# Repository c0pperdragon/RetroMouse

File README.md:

# RetroMouse
Adapter to attach PS/2 compatible mice to retro computers

## Motivation

I wanted to try to make such an adapter using one attiny1604 microcontroller 
with only the minimum additional circuitry.
This part also was one of the few that mouser actually had in stock.

## Mouse compatibility

The USB socket suggests that any USB mouse can be used, but that is actually not true. In 
reality the adapter only supports the simpler PS/2 interface protocol which can be handled by
regular microcontrollers just well.

For this to work, the mouse must be able to optionally support PS/2 if needed. Luckily this
compatibility is present in quite many devices, especially in the cheap and simple variants.
Unluckily on the other hand, this compatibilty depends on the specific controller IC the
manufacturer used for the mouse and can not really be guessed from the outside.
When PS/2 compatibility is not directly advertised, the only thing to do is just try.

## Arduino development

The microcontroller is supported by the Arduino IDE (using the megaTinyCore add-on).
To modify the firmware, you need a programmer device to re-flash the microcontroller
using the UDPI pin. Details on this process are available on the megaTinyCore webpage.

## Compatibility

This adapter works with Amiga and C64 computers and can auto-detect the host machine.
Further machines (for example Atari ST) may be supported in the future. 

## C64 input modes

From power-up, the adapter emulates the Commodore 1351 mouse. If you want to 
emulate a pair of paddles instead (to play Arkanoid, for example) hold down the right mouse button 
and click the left button 5 times. Doing the same thing with 6 left clicks switches back
to standard mode.

## Attention! No Hot-Plugging

The adapter is not designed to be hot-plugged into the host machine or the mouse to be hot-plugged
into the adapter. Make sure to always power down the host when changing configuration.

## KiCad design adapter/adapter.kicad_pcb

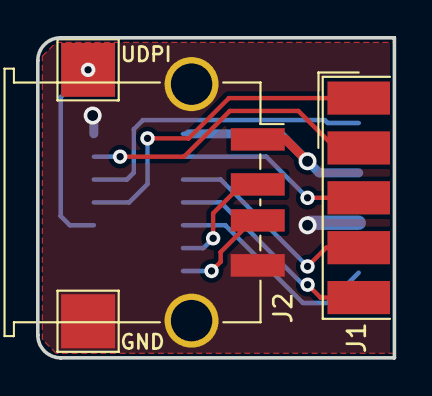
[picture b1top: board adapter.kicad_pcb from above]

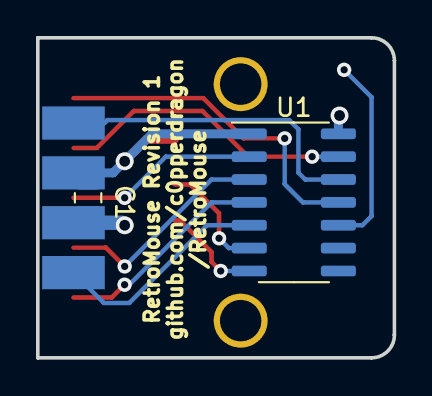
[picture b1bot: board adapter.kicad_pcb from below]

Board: 2 copper layers, 19.8 x 17.8 mm, 6 parts (2 on the bottom side), 12 nets.

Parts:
C1: 10uF; C_0805_2012Metric_Pad1.18x1.45mm_HandSolder
J1: DB9_Female; DSUB-9_Female_EdgeMount_P2.77mm
J2: USB_A; USB_A_TE_292303-7_Horizontal
J3, J4: Conn_01x01; TestPoint_Pad_3.0x3.0mm
U1: ATtiny1604-SS; SOIC-14_3.9x8.7mm_P1.27mm

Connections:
+5V: C1.1, J1.7, J2.1 (VBUS), U1.1 (VCC)
/CLOCK: J2.3 (D+), U1.7 (PB2)
/DATA: J2.2 (D-), U1.6 (PB3)
/UDPI: J4.1, U1.10 (~RESET/PA0)
GND: C1.2, J1.8, J2.4 (GND), J2.5 (Shield), J3.1, U1.14 (GND)
unnamed: J1.1, U1.11 (PA1)
unnamed: J1.2, U1.13 (PA3)
unnamed: J1.3, U1.2 (PA4)
unnamed: J1.4, U1.3 (PA5)
unnamed: J1.5, U1.4 (PA6)
unnamed: J1.6, U1.12 (PA2)
unnamed: J1.9, U1.5 (PA7)

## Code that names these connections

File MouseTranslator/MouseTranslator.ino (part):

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#include "PS2MouseHandler.h"

#define DEBUG       PIN_PB1
#define MOUSE_DATA  PIN_PB3
#define MOUSE_CLOCK PIN_PB2
                                 // C64      Amiga mouse
#define SUBD_PIN1   PIN_PA1      // up       mouse v
#define SUBD_PIN2   PIN_PA3      // down     mouse h
#define SUBD_PIN3   PIN_PA4      // left     mouse vq
#define SUBD_PIN4   PIN_PA5      // right    mouse hq
#define SUBD_PIN5   PIN_PA6      // pot y    middle button
#define SUBD_PIN6   PIN_PA2      // button   left buttonm
#define SUBD_PIN9   PIN_PA7      // pot x    right button

#define MODE_AMIGA    1
#define MODE_C64      2
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    if (emulate_pots || count)
    {
        VREF.CTRLA = 0x00;         // use 0.55V as VREF for the AC
        AC0.MUXCTRLA = 0x02;       // compare PA7 against voltage reference
        AC0.CTRLA = 0x27;          // trigger at negative edge, maximum hysteresis
        AC0.INTCTRL = 0x01;        // enable AC interrupt 
    }    
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    TCA0.SINGLE.CMP0BUF = x;
    TCA0.SINGLE.CMP1BUF = y;
}
// triggered when PA7 (PIN_SUBD9) goes low 
ISR (AC0_AC_vect) 
{
    if (countedges) 
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
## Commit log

2022-08-29 Collect information
2022-09-04 Amiga mouse emulation
2022-09-07 Paddle emulation
2022-09-08 Reduce timing jitter caused by interrupts
2022-09-08 Remove external pull-ups for mouse clock and data lines.
2022-09-24 Design PCB and adjust code
2022-10-03 Autodetect machine. Manual C64 mode switching.
2022-10-12 Fail to support atari paddles.
2022-10-14 Auto-adjust to C64/NTSC C64
2022-10-19 Docu
2023-01-22 Add warning to not hot-plug the device.
